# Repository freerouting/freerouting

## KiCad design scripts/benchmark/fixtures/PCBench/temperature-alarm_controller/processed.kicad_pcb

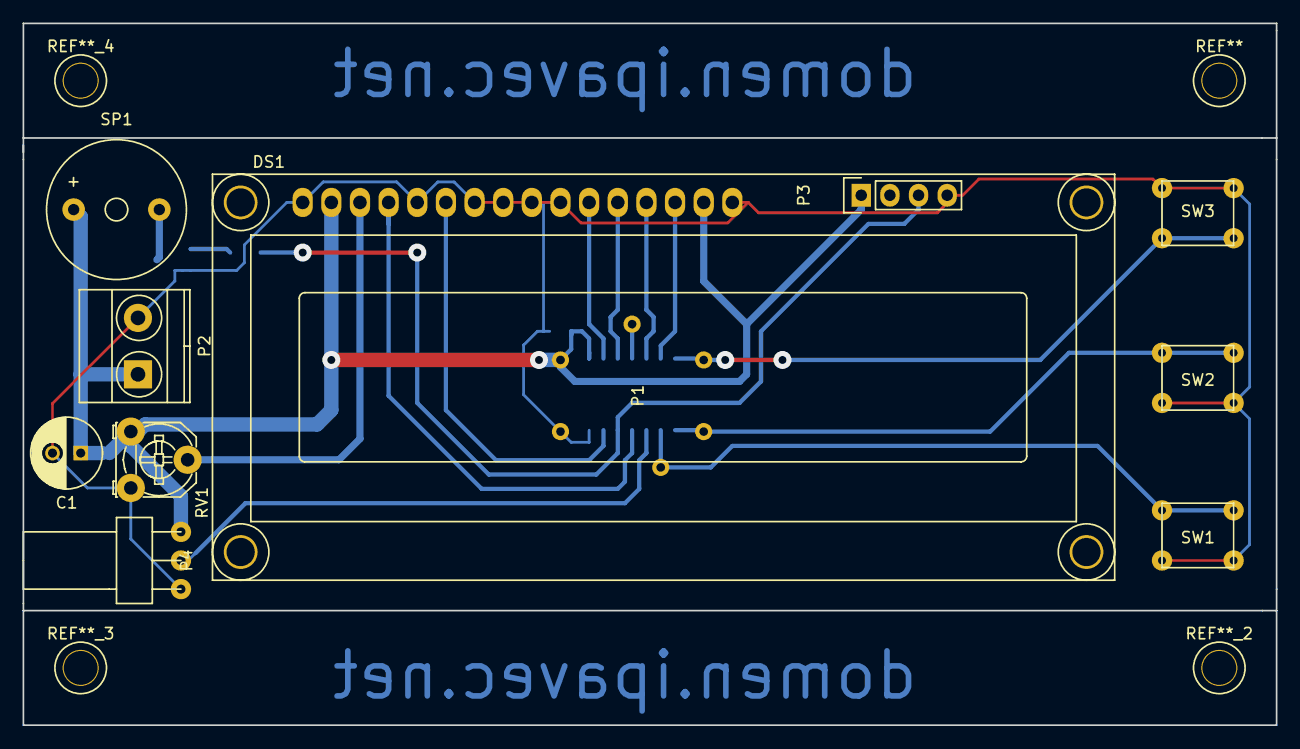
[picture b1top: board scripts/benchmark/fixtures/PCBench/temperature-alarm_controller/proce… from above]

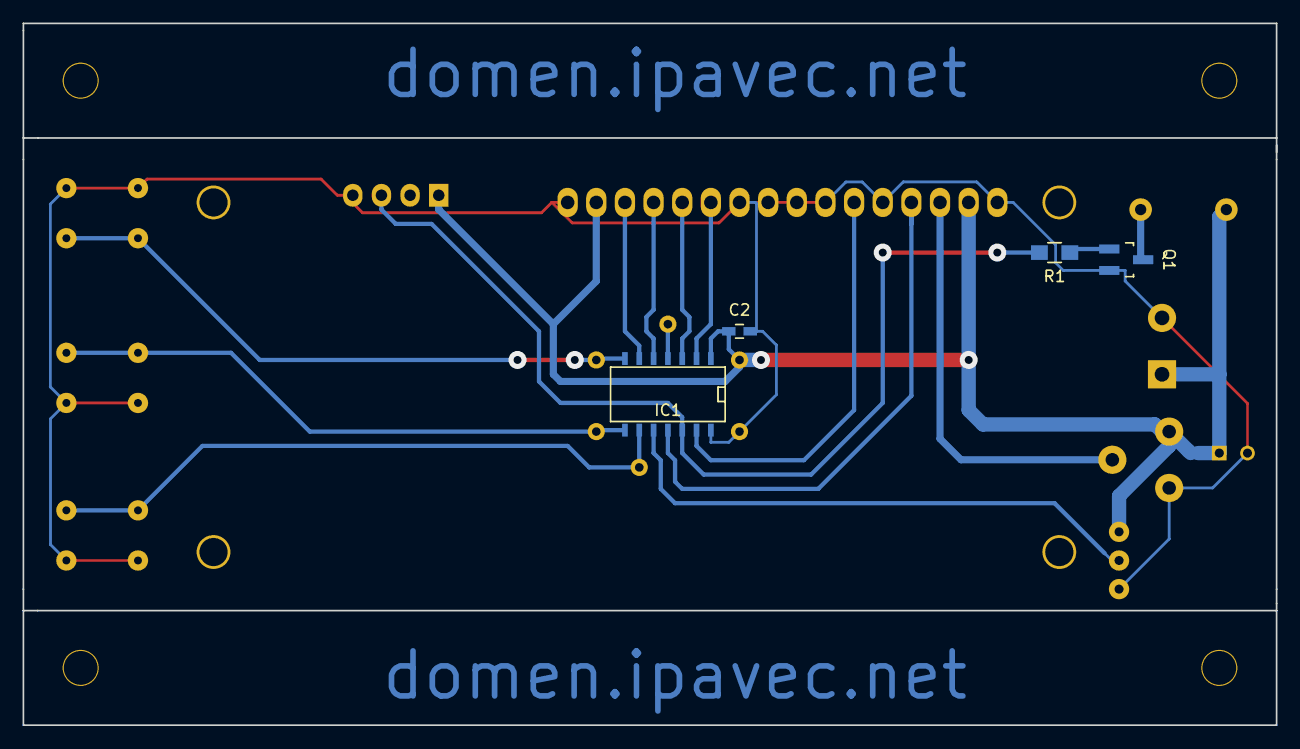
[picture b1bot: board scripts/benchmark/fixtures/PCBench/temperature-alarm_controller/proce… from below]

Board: 2 copper layers, 111.1 x 62.2 mm, 15 parts (4 on the bottom side), 17 nets.

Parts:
C1: 100uF; C_Radial_D6.3_L11.2_P2.5
C2: 100nF; C_0603_HandSoldering
DS1: LCD16X2; WC1602A
IC1: ATTINY841-SSU; SOIC-14_N
P1: CONN_01X06; ATTINY841-SPI
P2: CONN_01X02; TerminalBlock_Pheonix_MKDS1.5-2pol
P3: CONN_01X04; Pin_Header_Straight_1x04
P4: CONN_01X03; fanconnector
Q1: Q_NPN_BEC; SOT-23_Handsoldering
R1: 4k7; R_0805_HandSoldering
RV1: POT; Potentiometer_Triwood_RM-065
SP1: SPEAKER; Buzzer_12x9.5RM7.6
SW1, SW2, SW3: SW_PUSH; pushbutton

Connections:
+5V: C1.1, C2.1, DS1.2, DS1.15, IC1.1, P1.2, P2.1, P3.1, P4.3, RV1.1, SP1.1
AVR_MISO: IC1.8, P1.1, SW2.2
AVR_MOSI: IC1.7, P1.4, SW3.2
AVR_RESET: IC1.4, P1.5
AVR_SCK: IC1.9, P1.3, SW1.2
D4: DS1.11, IC1.2
D5: DS1.12, IC1.3
D6: DS1.13, IC1.5
D7: DS1.14, IC1.6
DQ: IC1.10, P4.2
E: DS1.6, IC1.13
GND: C1.2, C2.2, DS1.1, DS1.5, DS1.7, DS1.8, DS1.9, DS1.10, DS1.16, IC1.14, P1.6, P2.2, P3.4, P4.1, Q1.2, RV1.3, SW1.1, SW2.1, SW3.1
unnamed: DS1.3, RV1.2
unnamed: Q1.1, R1.1
unnamed: Q1.3, SP1.2
RS: DS1.4, IC1.11
TXD: IC1.12, P3.3, R1.2

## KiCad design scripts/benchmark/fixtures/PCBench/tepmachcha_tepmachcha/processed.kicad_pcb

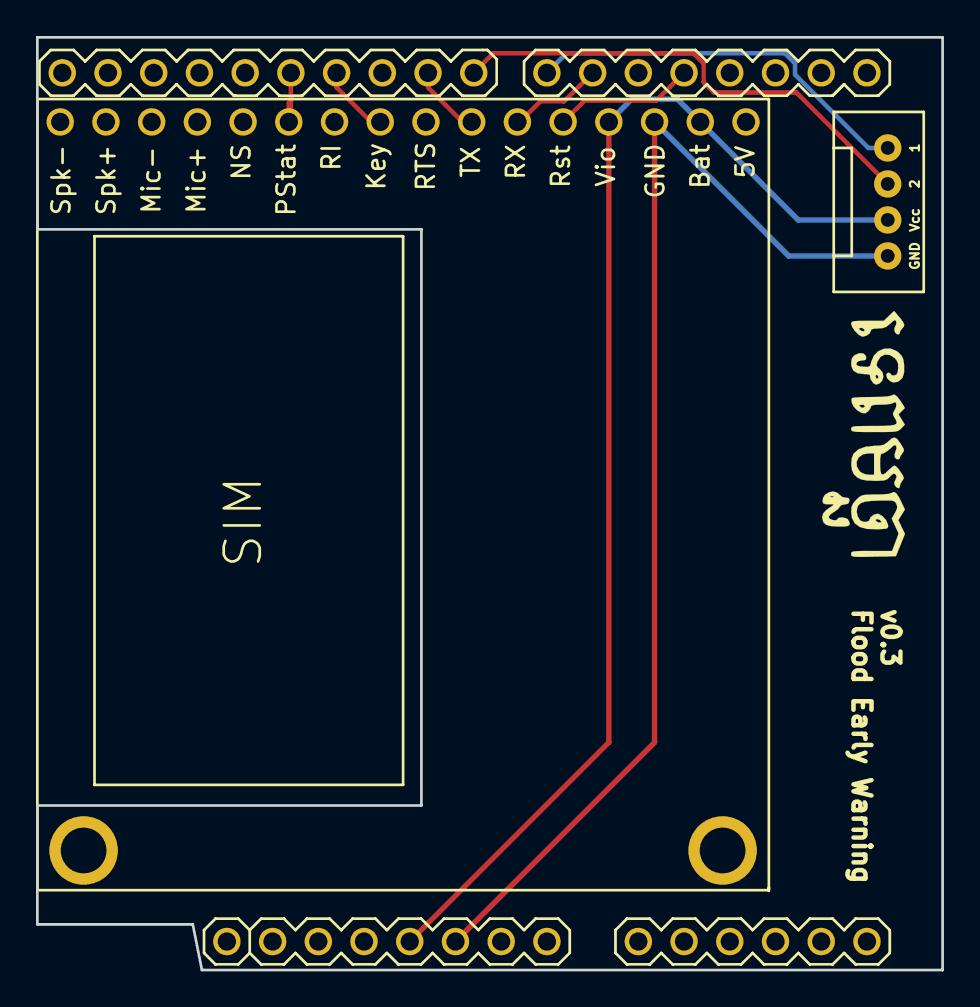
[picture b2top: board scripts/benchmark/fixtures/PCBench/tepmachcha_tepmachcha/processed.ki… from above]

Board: 2 copper layers, 50.3 x 51.8 mm, 3 parts (0 on the bottom side), 9 nets.

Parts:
P1: CONN_01X04; Grove_straight
SHIELD1: ARDUINO_SHIELD; ARDUINO
U1: FONA_808

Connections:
GND: P1.4, SHIELD1.GND1, U1.3
unnamed: P1.1, SHIELD1.7
unnamed: P1.2, SHIELD1.8
unnamed: SHIELD1.4, U1.5
unnamed: SHIELD1.6, U1.6
unnamed: SHIELD1.9, U1.7
unnamed: SHIELD1.11, U1.9
unnamed: SHIELD1.12, U1.11
VCC: P1.3, SHIELD1.5V, U1.2, U1.4

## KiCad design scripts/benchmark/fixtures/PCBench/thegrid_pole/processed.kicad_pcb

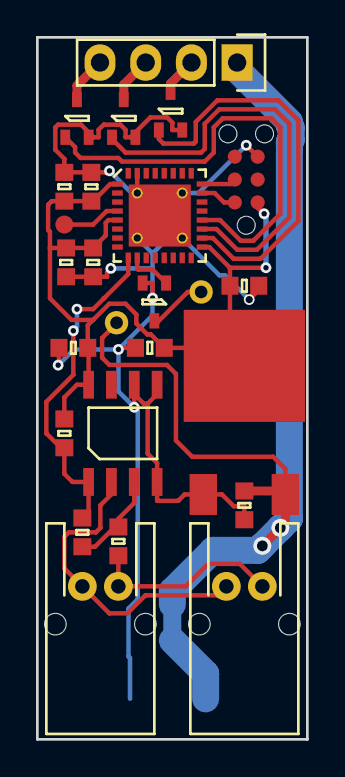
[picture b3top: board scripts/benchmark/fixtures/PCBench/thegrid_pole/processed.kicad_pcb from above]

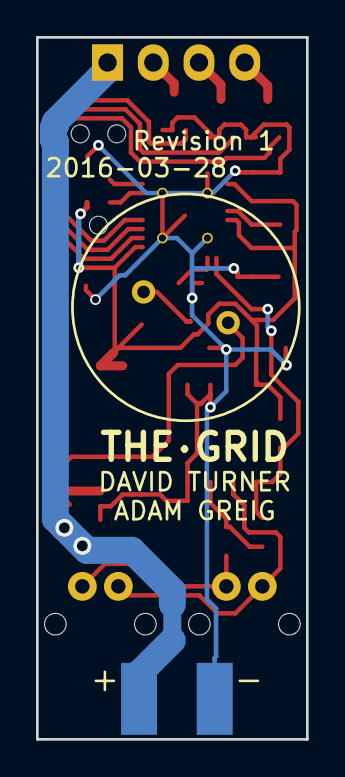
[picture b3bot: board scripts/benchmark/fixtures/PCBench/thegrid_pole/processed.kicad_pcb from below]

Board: 2 copper layers, 15.0 x 39.0 mm, 25 parts (2 on the bottom side), 18 nets.

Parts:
C1, C3, C5, C6: 100n; 0603
C2: 4u7; 0603
C4: 10n; 0603
C7: 10u; 0603
C8: 1u; 0603
IC1: LMx93; SOIC-8
IC2: STM32F0xxKxUx; QFN-32-EP-ST
P1: POWER_IN; minipow_edge
P2: BUS_IN; S02B-PASK-2
P3: BUS_OUT; S02B-PASK-2
P4: SWD_TC; TC2030-NL
P5: LEDs; Pin_Header_Straight_1x04
Q1, Q2, Q3, Q4: MTM232270LBF; SOT-323
R1, R2: 10k; 0603
R3: 1M; 0603
SP1: SPEAKER; piezo
TP1: RST; TESTPAD
U1: LD1117S33TR; TO-252-3

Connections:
+3V3: C1.2, C2.1, C3.1, C4.1, C5.1, C7.1, C8.1, IC1.8, IC2.1, IC2.5, IC2.17, P4.1, R1.1, U1.2
+12V: C6.1, P1.2, P5.1, SP1.1, U1.3
/BUS: IC1.1, IC2.9, R1.2, R3.1
/BUS_A: IC1.2, P2.1, P3.1
/BUS_B: P2.2, P3.2, R2.2
/DRIVE_B: P5.4, Q3.3
/DRIVE_G: P5.3, Q2.3
/DRIVE_R: P5.2, Q1.3
/LED_B: IC2.20, Q3.1
/LED_G: IC2.19, Q2.1
/LED_R: IC2.18, Q1.1
/PIEZO: IC2.10, Q4.1
/SWDCLK: IC2.24, P4.4
/SWDIO: IC2.23, P4.2
GND: C1.1, C2.2, C3.2, C4.2, C5.2, C6.2, C7.2, C8.2, IC1.4, IC1.5, IC1.6, IC2.31, IC2.EP, P1.1, P4.5, Q1.2, Q2.2, Q3.2, Q4.2, U1.1
unnamed: IC1.3, R2.1, R3.2
unnamed: IC2.4, TP1.1
unnamed: Q4.3, SP1.2
